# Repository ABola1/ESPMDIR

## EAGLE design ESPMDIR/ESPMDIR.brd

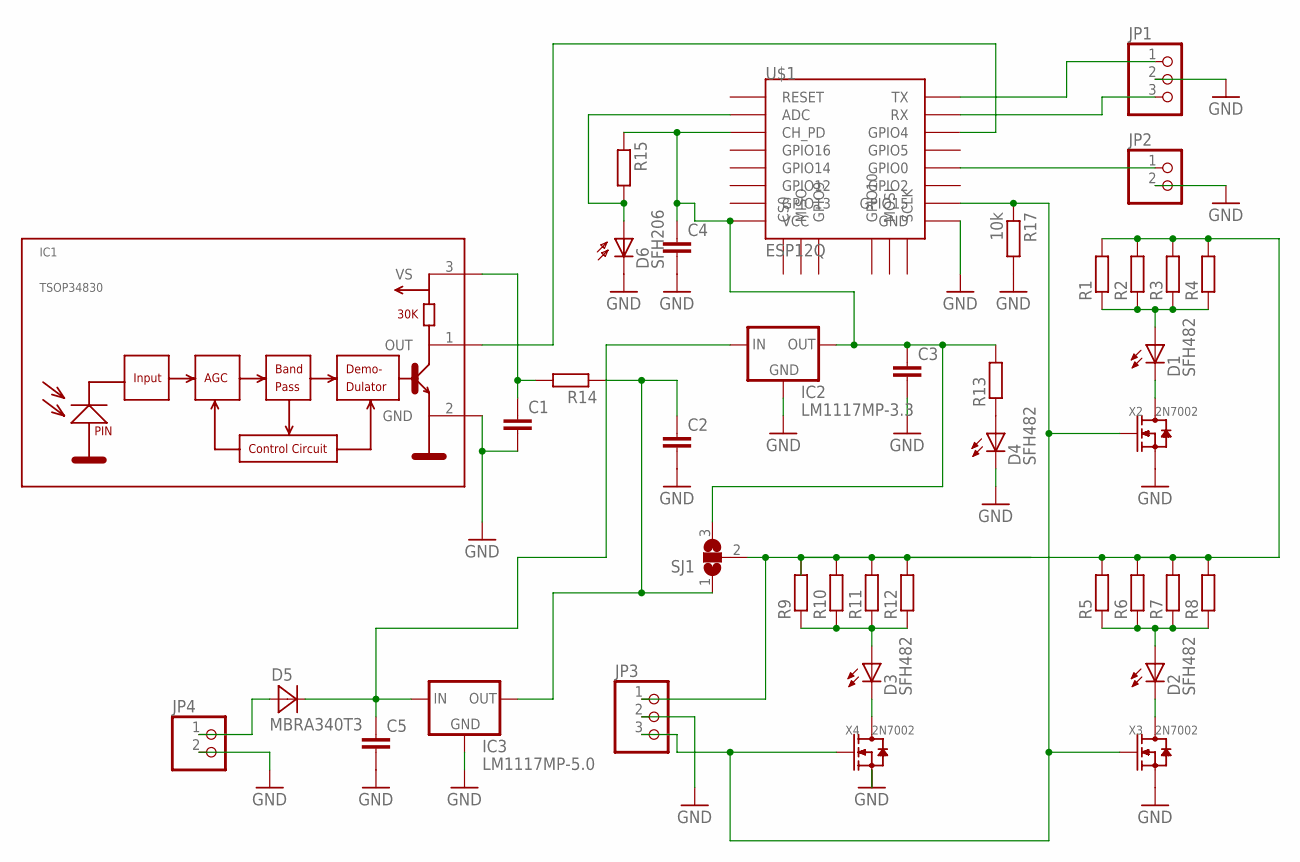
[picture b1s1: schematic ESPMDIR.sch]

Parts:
C1, C2, C3, C5: C-EUC4532; C4532
C4: C-EUC0805; C0805
D1, D2, D3, D4: SFH482
D5: MBRA340T3; SMA
D6: SFH206
IC1: TSOP34830; TSOP348
IC2: LM1117MP-3.3; SOT223
IC3: LM1117MP-5.0; SOT223
JP1, JP3: PINHD-1X3; 1X03
JP2, JP4: PINHD-1X2; 1X02
R1, R2, R3, R4, R5, R6, R7, R8, R9, R10, R11, R12, R13, R14, R15: R-EU_R0805; R0805
R17: 10k; R0805
SJ1: SJ2W; SJ_2
U$1: ESP12Q
X2, X3, X4: 2N7002; SOT-23

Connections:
unnamed: D1.K (C), X2.3 (D)
unnamed: R9.2, R10.2, R11.2, R12.2
unnamed: D3.A, R9.1, R10.1, R11.1, R12.1
unnamed: D2.K (C), X3.3 (D)
unnamed: C3.1, C4.1, IC2.2 (OUT), IC2.4 (OUT), R13.2, R15.1, SJ1.3, U$1.CH_PD, U$1.VCC
unnamed: D1.A, R1.1, R2.1, R3.1, R4.1
unnamed: D2.A, R5.1, R6.1, R7.1, R8.1
unnamed: D3.K (C), X4.3 (D)
unnamed: JP3.3, R17.1, U$1.GPIO15, X2.1 (G), X3.1 (G), X4.1 (G)
unnamed: C2.1, IC3.2 (OUT), IC3.4 (OUT), R14.1, SJ1.1
unnamed: JP1.1, U$1.TX
unnamed: JP3.1, R1.2, R2.2, R3.2, R4.2, R5.2, R6.2, R7.2, R8.2, SJ1.2
unnamed: JP1.3, U$1.RX
unnamed: JP2.1, U$1.GPIO0
unnamed: D4.A, R13.1
unnamed: C1.1, IC1.3 (VS), R14.2
unnamed: IC1.1 (OUT), U$1.GPIO4
unnamed: C1.2, C2.2, C3.2, C4.2, C5.2, D4.K (C), D6.K (C), IC1.2 (GND), IC2.1 (GND), IC3.1 (GND), JP1.2, JP2.2, JP3.2, JP4.2, R17.2, U$1.GND, X2.2 (S), X3.2 (S), X4.2 (S)
unnamed: D5.A, JP4.1
unnamed: C5.1, D5.C, IC2.3 (IN), IC3.3 (IN)
unnamed: D6.A, R15.2, U$1.ADC

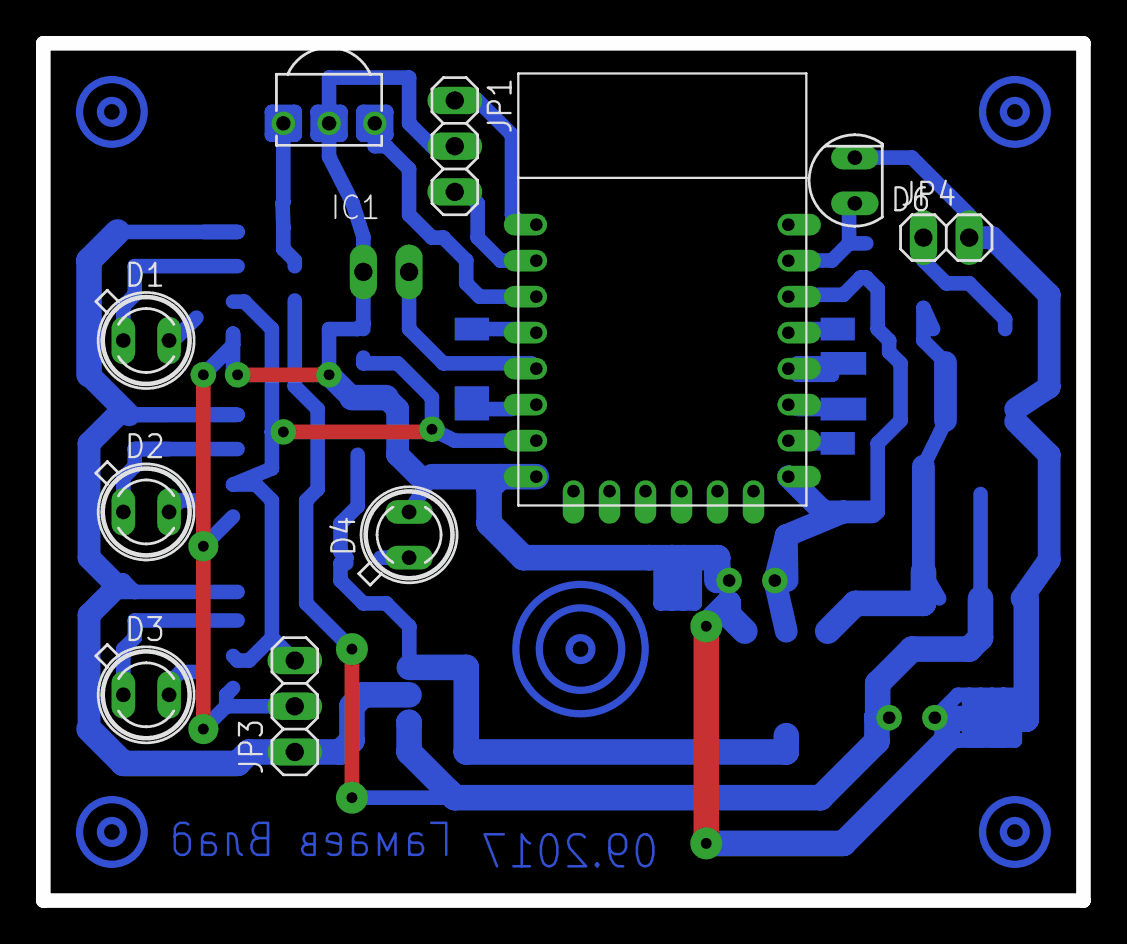
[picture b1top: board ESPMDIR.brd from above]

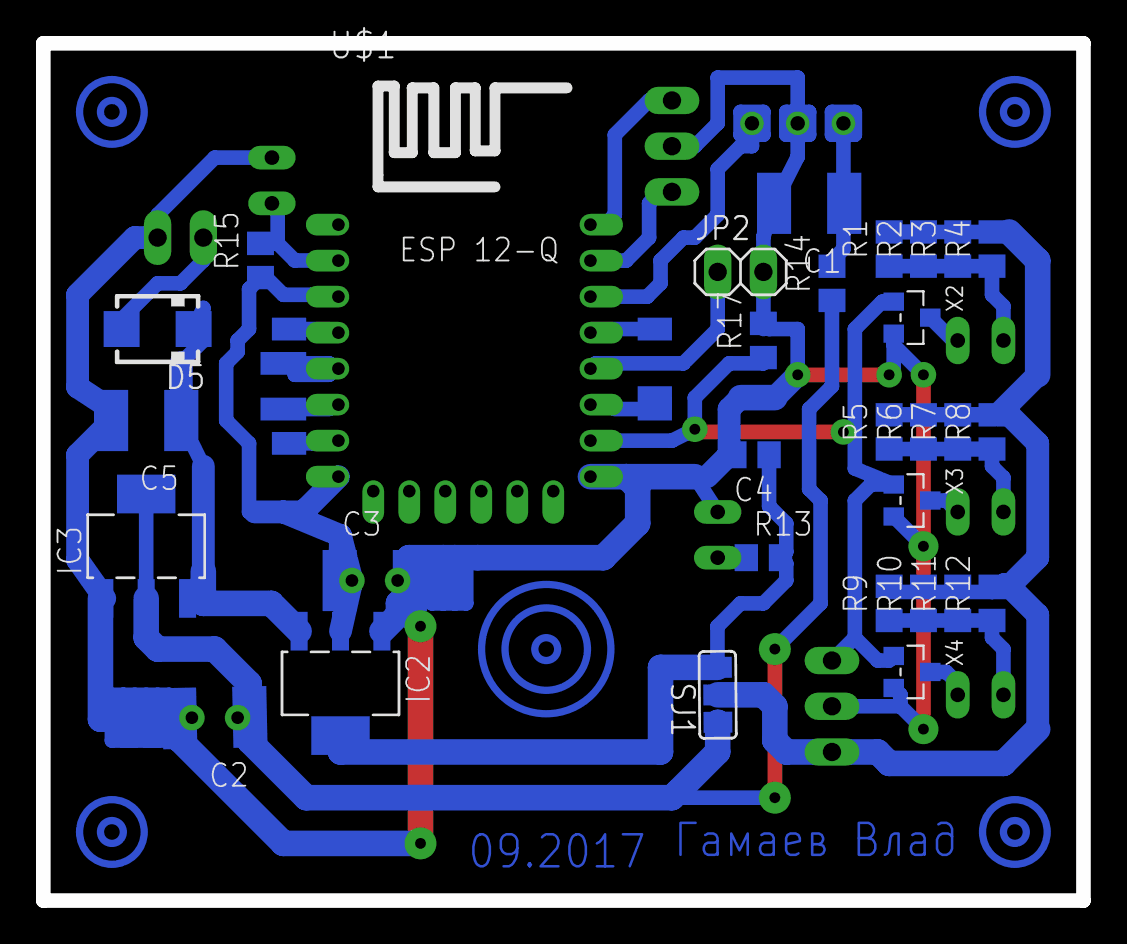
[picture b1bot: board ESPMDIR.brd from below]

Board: 2 copper layers, 57.8 x 47.6 mm, 39 parts (30 on the bottom side), 21 nets.

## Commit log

2017-08-26 :octocat: Added .gitattributes & .gitignore files
2017-09-08 08092017
2017-09-11 11092017
